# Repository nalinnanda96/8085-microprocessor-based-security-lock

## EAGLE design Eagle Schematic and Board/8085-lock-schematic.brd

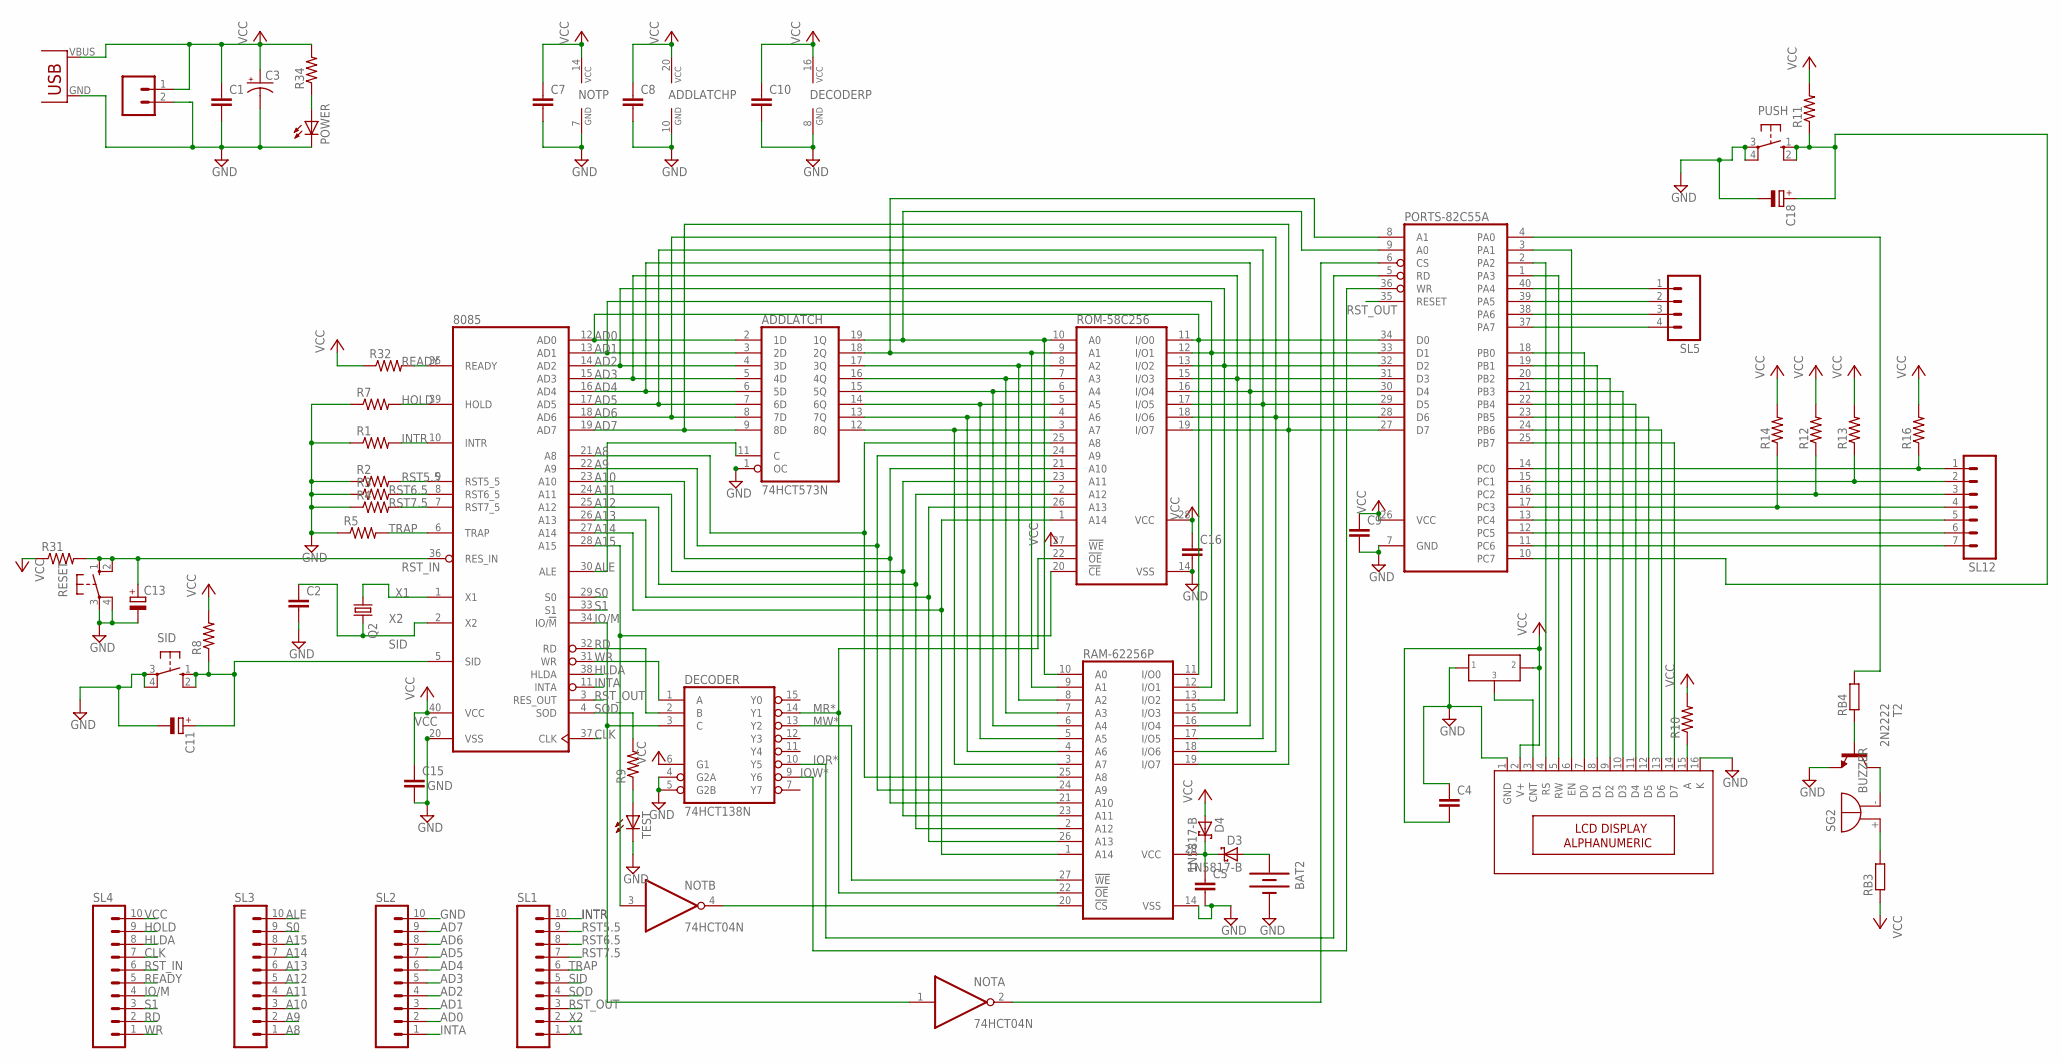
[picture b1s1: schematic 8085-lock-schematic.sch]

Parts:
8085: 8085; DIL40
ADDLATCH: 74HCT573N; DIL20
BAT2: BATTERY20PTH; BATTCOM_20MM_PTH
C1, C2, C4, C5, C7, C8, C9, C10, C15, C16: C-EU025-024X044; C025-024X044
C3: CPOL-USE2.5-5; E2,5-5
C11, C13, C18: CPOL-EUE2.5-6; E2,5-6
D3, D4: 1N5817-B; DO41-7.6
DECODER: 74HCT138N; DIL16
NOT: 74HCT04N; DIL14
PORTS-82C55A: 82C55A; DIL40
POWER: LED5MM
PUSH: 10-XX; B3F-10XX
Q2: CRYSTALHC49US; HC49US
R1, R2, R3, R4, R5, R7, R8, R9, R10, R11, R12, R13, R14, R16, R31, R32, R34: R-US_0207/7; 0207/7
R6: PRESET_LR
RAM-62256P: 62256P; DIL28-6
RB3, RB4: R-EU_0204/7; 0204/7
RESET: 10-XX; B3F-10XX
ROM-58C256: 58C256P; DIL28-6
SG2: BUZZER; F/TMB
SID: 10-XX; B3F-10XX
SL1, SL2, SL3, SL4: M10; 10P
SL5: M04; 04P
SL12: M07; 07P
T2: 2N2222; TO18
TEST: LED5MM
U$1: M02; 02P
U$2: USB(POWER)
U$3: LCD-16X2; 16X2-LCD-WITH-MOUNT

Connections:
A8: 8085.21 (A8), RAM-62256P.25 (A8), ROM-58C256.25 (A8), SL3.1
A9: 8085.22 (A9), RAM-62256P.24 (A9), ROM-58C256.24 (A9), SL3.2
A10: 8085.23 (A10), RAM-62256P.21 (A10), ROM-58C256.21 (A10), SL3.3
A11: 8085.24 (A11), RAM-62256P.23 (A11), ROM-58C256.23 (A11), SL3.4
A12: 8085.25 (A12), RAM-62256P.2 (A12), ROM-58C256.2 (A12), SL3.5
A13: 8085.26 (A13), RAM-62256P.26 (A13), ROM-58C256.26 (A13), SL3.6
A14: 8085.27 (A14), RAM-62256P.1 (A14), ROM-58C256.1 (A14), SL3.7
A15: 8085.28 (A15), NOT.3 (I), ROM-58C256.20 (!CE), SL3.8
AD0: 8085.12 (AD0), ADDLATCH.2 (1D), PORTS-82C55A.34 (D0), RAM-62256P.11 (I/O0), ROM-58C256.11 (I/O0), SL2.2
AD1: 8085.13 (AD1), ADDLATCH.3 (2D), PORTS-82C55A.33 (D1), RAM-62256P.12 (I/O1), ROM-58C256.12 (I/O1), SL2.3
AD2: 8085.14 (AD2), ADDLATCH.4 (3D), PORTS-82C55A.32 (D2), RAM-62256P.13 (I/O2), ROM-58C256.13 (I/O2), SL2.4
AD3: 8085.15 (AD3), ADDLATCH.5 (4D), PORTS-82C55A.31 (D3), RAM-62256P.15 (I/O3), ROM-58C256.15 (I/O3), SL2.5
AD4: 8085.16 (AD4), ADDLATCH.6 (5D), PORTS-82C55A.30 (D4), RAM-62256P.16 (I/O4), ROM-58C256.16 (I/O4), SL2.6
AD5: 8085.17 (AD5), ADDLATCH.7 (6D), PORTS-82C55A.29 (D5), RAM-62256P.17 (I/O5), ROM-58C256.17 (I/O5), SL2.7
AD6: 8085.18 (AD6), ADDLATCH.8 (7D), PORTS-82C55A.28 (D6), RAM-62256P.18 (I/O6), ROM-58C256.18 (I/O6), SL2.8
AD7: 8085.19 (AD7), ADDLATCH.9 (8D), PORTS-82C55A.27 (D7), RAM-62256P.19 (I/O7), ROM-58C256.19 (I/O7), SL2.9
ALE: 8085.30 (ALE), ADDLATCH.11 (C), SL3.10
BUZZER: PORTS-82C55A.4 (PA0), RB4.2
CLK: 8085.37 (CLK), SL4.7
GND: 8085.20 (VSS), ADDLATCH.1 (OC), ADDLATCH.10 (GND), BAT2.2 (-), C1.2, C2.2, C3.-, C4.1, C5.2, C7.2, C8.2, C9.2, C10.2, C11.-, C13.-, C15.2, C16.2, C18.-, DECODER.4 (G2A), DECODER.5 (G2B), DECODER.8 (GND), NOT.7 (GND), PORTS-82C55A.7 (GND), POWER.K (C), PUSH.3, PUSH.4 (P1), R1.1, R2.1, R3.1, R4.1, R5.1, R6.P$1 (1), R7.1, RAM-62256P.14 (VSS), RESET.3, RESET.4 (P1), ROM-58C256.14 (VSS), SID.3, SID.4 (P1), SL2.10, T2.1 (E), TEST.K (C), U$1.2, U$2.GND, U$3.1 (GND), U$3.16 (K)
HLDA: 8085.38 (HLDA), SL4.8
HOLD: 8085.39 (HOLD), R7.2, SL4.9
INTA: 8085.11 (INTA), SL2.1
INTR: 8085.10 (INTR), R1.2, SL1.10
IO/M: 8085.34 (IO/!M), DECODER.3 (C), NOT.1 (I), SL4.4
IOR*: DECODER.10 (Y5), PORTS-82C55A.5 (RD)
IOW*: DECODER.9 (Y6), PORTS-82C55A.36 (WR)
MR*: DECODER.14 (Y1), RAM-62256P.22 (!OE), ROM-58C256.22 (!OE)
MW*: DECODER.13 (Y2), RAM-62256P.27 (!WE)
unnamed: PORTS-82C55A.14 (PC0), R16.1, SL12.1
unnamed: PORTS-82C55A.15 (PC1), R13.1, SL12.2
unnamed: PORTS-82C55A.16 (PC2), R12.1, SL12.3
unnamed: PORTS-82C55A.17 (PC3), R14.1, SL12.4
unnamed: PORTS-82C55A.13 (PC4), SL12.5
unnamed: PORTS-82C55A.12 (PC5), SL12.6
unnamed: PORTS-82C55A.11 (PC6), SL12.7
unnamed: PORTS-82C55A.40 (PA4), SL5.1
unnamed: R10.1, U$3.15 (A)
unnamed: R6.P$3 (3), U$3.3 (CNT)
unnamed: C5.1, D3.C, D4.C, RAM-62256P.28 (VCC)
unnamed: ADDLATCH.17 (3Q), RAM-62256P.8 (A2), ROM-58C256.8 (A2)
unnamed: ADDLATCH.16 (4Q), RAM-62256P.7 (A3), ROM-58C256.7 (A3)
unnamed: ADDLATCH.15 (5Q), RAM-62256P.6 (A4), ROM-58C256.6 (A4)
unnamed: ADDLATCH.14 (6Q), RAM-62256P.5 (A5), ROM-58C256.5 (A5)
unnamed: ADDLATCH.13 (7Q), RAM-62256P.4 (A6), ROM-58C256.4 (A6)
unnamed: ADDLATCH.12 (8Q), RAM-62256P.3 (A7), ROM-58C256.3 (A7)
unnamed: PORTS-82C55A.39 (PA5), SL5.2
unnamed: PORTS-82C55A.38 (PA6), SL5.3
unnamed: PORTS-82C55A.37 (PA7), SL5.4
unnamed: PORTS-82C55A.25 (PB7), U$3.14 (D7)
unnamed: NOT.2 (O), PORTS-82C55A.6 (CS)
unnamed: PORTS-82C55A.2 (PA2), U$3.4 (RS)
unnamed: PORTS-82C55A.1 (PA3), U$3.5 (RW)
unnamed: PORTS-82C55A.24 (PB6), U$3.13 (D6)
unnamed: PORTS-82C55A.23 (PB5), U$3.12 (D5)
unnamed: POWER.A, R34.1
unnamed: PORTS-82C55A.22 (PB4), U$3.11 (D4)
unnamed: PORTS-82C55A.21 (PB3), U$3.10 (D3)
unnamed: PORTS-82C55A.20 (PB2), U$3.9 (D2)
unnamed: PORTS-82C55A.19 (PB1), U$3.8 (D1)
unnamed: PORTS-82C55A.18 (PB0), U$3.7 (D0)
unnamed: PORTS-82C55A.3 (PA1), U$3.6 (EN)
unnamed: R9.1, TEST.A
unnamed: NOT.4 (O), RAM-62256P.20 (!CS)
unnamed: ADDLATCH.19 (1Q), PORTS-82C55A.9 (A0), RAM-62256P.10 (A0), ROM-58C256.10 (A0)
unnamed: ADDLATCH.18 (2Q), PORTS-82C55A.8 (A1), RAM-62256P.9 (A1), ROM-58C256.9 (A1)
unnamed: BAT2.1 (+), D3.A
unnamed: RB4.1, T2.2 (B)
unnamed: SG2.-, T2.3 (C)
unnamed: RB3.2, SG2.+
RD: 8085.32 (RD), DECODER.2 (B), SL4.2
READY: 8085.35 (READY), R32.2, SL4.5
RST5.5: 8085.9 (RST5_5), R2.2, SL1.9
RST6.5: 8085.8 (RST6_5), R3.2, SL1.8
RST7.5: 8085.7 (RST7_5), R4.2, SL1.7
RST_IN: 8085.36 (RES_IN), C13.+, R31.2, RESET.1 (S), RESET.2 (S1), SL4.6
RST_OUT: 8085.3 (RES_OUT), PORTS-82C55A.35 (RESET), SL1.3
S0: 8085.29 (S0), SL3.9
S1: 8085.33 (S1), SL4.3
SID: 8085.5 (SID), C11.+, R8.1, SID.1 (S), SID.2 (S1), SL1.5
SID1: C18.+, PORTS-82C55A.10 (PC7), PUSH.1 (S), PUSH.2 (S1), R11.1
SOD: 8085.4 (SOD), R9.2, SL1.4
TRAP: 8085.6 (TRAP), R5.2, SL1.6
VCC: 8085.40 (VCC), ADDLATCH.20 (VCC), C1.1, C3.+, C4.2, C7.1, C8.1, C9.1, C10.1, C15.1, C16.1, D4.A, DECODER.6 (G1), DECODER.16 (VCC), NOT.14 (VCC), PORTS-82C55A.26 (VCC), R6.P$2 (2), R8.2, R10.2, R11.2, R12.2, R13.2, R14.2, R16.2, R31.1, R32.1, R34.2, RB3.1, ROM-58C256.27 (!WE), ROM-58C256.28 (VCC), SL4.10, U$1.1, U$2.VBUS (VCC), U$3.2 (V+)
WR: 8085.31 (WR), DECODER.1 (A), SL4.1
X1: 8085.1 (X1), Q2.1, SL1.1
X2: 8085.2 (X2), C2.1, Q2.2, SL1.2

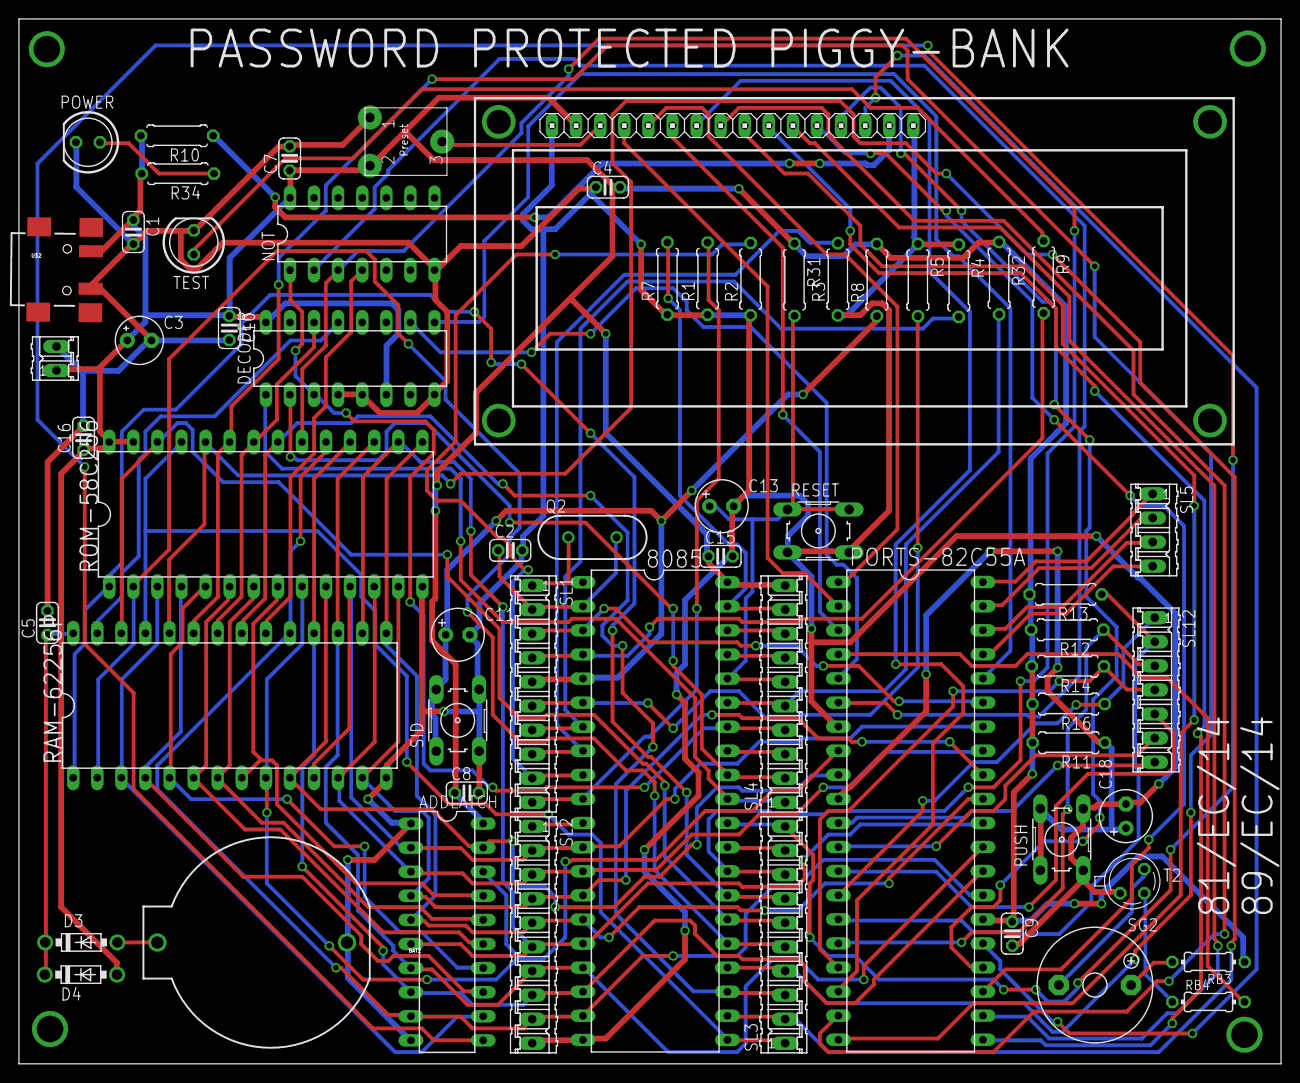
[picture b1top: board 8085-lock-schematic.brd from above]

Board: 2 copper layers, 133.1 x 110.2 mm, 61 parts (0 on the bottom side), 87 nets.

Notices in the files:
parts and their libraries:
SparkFun-Electromechanical: Licensing: Creative Commons ShareAlike 4.0 International - https://creativecommons.org/licenses/by-sa/4.0
